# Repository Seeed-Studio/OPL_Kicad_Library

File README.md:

# Welcome to Our Hardware Component Repository!

Dive into a world of innovation with our curated collection of hardware components straight from the electronics hub of Shenzhen, complemented by an array of parts supported by Seeed Studio. Our mission is to empower makers, developers, and hardware enthusiasts with a diverse repository that streamlines innovation and accelerates development.

The Seeed Fusion Open Parts Libraries (OPL) and the associated component libraries are provided and maintained by the [Seeed Studio Fusion](https://www.seeedstudio.com/fusion.html) team and the wider community for the turnkey [Seeed Fusion PCB Assembly (PCBA) Service](https://www.seeedstudio.com/fusion_pcb.html).

**The XIAO Family**

To accelerate PCB design and make it much more convenient, Seeed Fusion has provided these component libraries for KiCad. Prepared and scrutinized by our own engineers, these footprints can save you hours of design time and minimize potential production errors, so you can get on with PCB design with peace of mind.

## Highlights(Content of Tables)

- [**Preparatory Work: KiCad Download and Library Download**](#jump1)
- [**How to add and use Seeed OPL Footprint Libraries(Grove Vision AI V2)**](#jump2)
- [**How to add and use Seeed OPL Symbol Libraries(Grove Vision AI V2)**](#jump3)
- [**Scale up Your Creation With Seeed Studio Fusion**](#jump4)
- [**Co-Create with Seeed Studio**](#jump5)
- [**Resources**](#jump6)

## <span id="jump1">Preparatory Work: KiCad Download and Library Download </span>

1. You can refer to this [link](https://www.kicad.org/download/) to download the KiCad software.

2. You can [download](https://github.com/Seeed-Studio/OPL_Kicad_Library) the "OPL_KiCad_Library" or use command to clone:

```
git clone https://github.com/Seeed-Studio/OPL_Kicad_Library.git
```

## How to add and use Seeed OPL Footprint Libraries

### <span id="jump2"> Take Grove Vision AI V2 and XIAO footprint as an Example </span>

1. Open KiCad and refer to `File -> Open Project`.

2. Find the "Grove Vision AI V2 Library" and open the project:

3. Double click the "Grove Vision AI V2" PCB file and you will see below:

4. Refer to the `Preferences -> Manage Footprint Libraries`

5. Here is the existed footprint libraries and you can click the button below:

6. Find the "Grove Vision AI V2 Library" and open the folder that contains the boards footprint:

Now you have added the "XIAO footprint library"

7. You can click here to use the added library:

8. Search for "seeed" and you can check the footprint added:

9. Click "ok" and you can add the XIAO RP2040 footprint into the "Grove Vision VI V2".

10. You can change any component on the Grove Vision VI V2 module and make it your own project.

## <span id="jump3"> How to add and use Seeed OPL Symbol Libraries </span>

### Take Grove Vision AI V2 and Sensor-Transducer as an Example:

1. Open KiCad and refer to `File -> Open Project`.

2. Find the "Grove Vision AI V2 Library" and open the project:

3. Double click the "Grove Vision AI V2" .sch file and you will see below:

4. Refer to the `Preferences -> Manage Symbol Libraries`

5. Here is the existed symbol libraries and you can click the button below:

6. Find the "OPL_Sensor-Transducer" lib file:

Now you have added the "OPL_Sensor-Transducer library"

7. You can click here to use the added library:

8. Search for "OPL" and you can check the symbol added:

9. Click "ok" and you can add it into the "Grove Vision VI V2".

10. You can change any component on the Grove Vision VI V2 module and make it your own project.

## <span id="jump4"> Scale up Your Creation With Seeed Studio Fusion </span>

Seeed Studio Fusion serves as the comprehensive service platform for Seeed Studio, a global one-stop online platform offering PCB manufacturing, PCB assembly and hardware customization with global sourcing capability. Whether you need prototyping, mass production, custom solutions for open-source products, or the transformation of your creative ideas into profitable products, Seeed Studio Fusion can meet your requirements.

- [PCB/PCBA Design](https://www.seeedstudio.com/fusion_pcb.html)
- [Fusion Website](https://www.seeedstudio.com/fusion.html)
- **Email Contact**: fusion@seeed.io

## <span id="jump5"> Co-Create with Seeed Studio </span>

Leverage our Co-Create Program to transform your advanced prototype into a commercially successful product! This program is designed to optimize your product's journey from prototype to market by handling marketing, packaging, and distribution, allowing you to concentrate on refining your product. Upon acceptance of your prototype by Seeed, it will be showcased on the Seeed Studio marketplace. You'll receive a portion of the profits for each unit sold.

- [Application Form](https://docs.google.com/forms/d/e/1FAIpQLSe3A7_rIbn2OLO4JyJd_poGZodItCaRy6M6-3FtdqL3xG1Usg/viewform)
- [Co-Create Website](https://www.seeedstudio.com/co-create.html)

## <span id="jump6"> Resources </span>

- [Seeed Studio Open Parts List](https://files.seeedstudio.com/wiki/OPL/OPL_list.xlsx)

<!-- ## Even More Components!

As of last December, the [OPL has expanded](http://www.seeedstudio.com/blog/2018/12/04/just-what-you-wanted-for-xmas-introducing-the-new-shenzhen-open-parts-library-with-over-10000-parts/) from 800 components to more than 10,000 with the introduction of the new Shenzhen OPL. The original Seeed OPL is a catalog of components from Seeed’s own inventory, we have the parts and, we have been using them in our own production processes for years. The Shenzhen OPL contains parts from Shenzhen’s biggest components distributor that Seeed can quickly order for turnkey PCBA. While the sources are different, both can be used together with the Seeed Fusion PCBA service and reduce the production time to 7 days.

But with all the new components and many more to come, we don’t have enough resources to create the footprints for all of them. So, we are asking for help from you and the wider community to gradually build-up the library with us. As more and more users utilize the OPL and update the component libraries, the better the library will become for everyone. 

To assist with the process, we have designated a team of engineers to maintain the library and GitHub repositories. They will also help draw some footprints and connect schematic symbols. But while our engineers do their best to check each footprint, with the sheer number of components, it is inevitable that some errors will be present. It is unavoidable. So to make up for it, Seeed Fusion has introduced a re-manufacture promise: If an error in the library requires the boards to be re-manufactured, then we will re-manufacture the corrected boards for you for free. By using this library, you accept this potential risk.

## Footprint Design Guidelines
It is still early days, and we have a lot of catching up to do. So, the most important additions at this stage are unique symbols and footprints and any generic footprints that are missing. Part-specific symbols that use generic footprints and slight variations of generic footprints can be added later.

For consistency and ease of use, we would greatly appreciate it if everyone followed the same guidelines for new additions to the library:

-	The previous component libraries have been re-organized to match the Shenzhen OPL’s categorization. Please add new entries to the relevant sub-library according to the online OPL library’s classification.
-	Please take the time to study [KiCad’s own Library Convention](http://kicad-pcb.org/libraries/klc/) and ensure that the new footprints comply. Please refer to other footprints in the OPL or KiCad’s built-in footprints for reference. 
-	For MPN specific footprints, please follow the existing footprint naming convention for the footprint and name the corresponding schematic symbol with the manufacturer part number.

### Notes:
- #### The current version of the KiCad Library has been completely revamped in response to all the feedback we have recieved. Originally a direct import of the Eagle library, the old library did not comply with KiCad guidelines and placed features on the wrong layers. For the latest version, we have throroughly investigated the issues and revised (nearly) all of the footprints. Let us know if you think we missed something!

-	The Seeed OPL component libraries have been updated to match the Shenzhen OPL categories to aid in merging the two libraries. Some components will have moved to new homes, but this has not been updated on the website OPL library yet. We will update this soon!
-	Some of the original Seeed OPL KiCad component footprints have not been updated to match KiCad’s design guidelines yet. They are safe to use, and the pads are correct, but they may look a little ugly.
-	Unlike previous versions, we have uploaded the files individually as opposed to a whole zip file. We hope this will help you follow standard GitHub workflow to contribute changes. (Thanks for your feedback!)

There is a lot to consider in managing a large library like this, so we would greatly appreciate any ideas and feedback regarding how we can make the library more user-friendly. We’ll be monitoring the discussion section and the designated OPL section in our forums. You are also welcome to let us know by [e-mail](mailto:fusion@seeed.cc).

We hope the new maintained library will prove to be an invaluable resource to all of our PCBA users and beyond.

## Resources
1. A KiCad Bill-of-Materials (BOM) plugin to follow SeeedStudio's Fusion PCBA assembly service's template, This plugin is set up to use the KiCad schematic's part data as it is provided in Seeed Studio's Open Parts Library (OPL) collection for KiCad. - https://github.com/imrehg/kicad-bom-seeedstudio

 -->

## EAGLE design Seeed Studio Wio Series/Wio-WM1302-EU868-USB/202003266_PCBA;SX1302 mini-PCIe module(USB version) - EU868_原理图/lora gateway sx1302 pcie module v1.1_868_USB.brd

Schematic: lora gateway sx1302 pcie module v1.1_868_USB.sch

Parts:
ANT1: U.FL-R-SMT-1(10); U-FL3P-SMD-2.6X2.6X1.0MM
ANT2: DNP; U-FL3P-SMD-2.6X2.6X1.0MM
C1, C12, C15, C19, C23, C25, C26, C29, C32, C41, C43, C45, C65, C67, C80, C83, C86, C88: 100nF; C0402
C2, C75: 2.2pF; C0402
C3, C92: 10uF; C0603
C4, C8, C11, C16, C17, C18, C64: 56pF; C0402
C5, C6, C9, C10: 3.6pF; C0402
C7, C91: 5.6pF; C0402
C13, C20, C21, C24, C28, C35, C39, C40, C42, C44, C47, C48, C76, C87, C89: 1uF; C0402
C14, C38, C57, C66, C81, C84: 10pF; C0402
C22, C27, C33: 10uF; C0603@1
C30, C56, C74, C77, C78, C79: DNP; C0402
C31: DNP; C0603@1
C34, C46, C63: 470nF; C0402
C36: 47nF; C0402
C37: 47pF; C0402
C49: 4.7uF; C0603
C50, C62, C85: 10nF; C0402
C51: 1nF; C0402
C52, C55: 100pF; C0402
C53, C60, C61: 3.3pF; C0402
C54: 39pF; C0402
C58: 1.3pF; C0402
C59, C68, C73: 1.8pF; C0402
C69, C70, C71, C72: 10uF; C0805
C82: 2.7pF; C0402
C90: 2.2uF; C0603
D1, D4: Green; LED-0402
D2: Red; LED-0402
D3: Blue; LED-0402
D5: LXES15AAA1-153; ESD-0402
D6: DNP; ESD-0402
D7: BAT54XV2T1G; SOD-523
FB1: BLM15PD121SN1D; F0402
J1: DNP; PCIE52P-0.8-50.95X30MM
L1: LQP15MN1N2B02D; L0402
L2: LQW15AN6N8G00D; L0402
L4: 0R; F0603
L5: LQH44PN1R0NP0L; L4.4X3.0MM
L6, L14, L20: MLZ2012M150WT; L0805
L7, L15, L18, L21: DNP; L0402
L8: LQW15AN3N0B00; L0402
L9: LQW15AN47NJ00D; L0402
L10: LQW15AN2N5B00D; L0402
L11: LQW15AN4N7C00D; L0402
L12, L13: LQW15AN12NG00D; L0402
L16: LQW15AN7N5G00D; L0402
L17, L24: LQW15AN5N6C10D; L0402
L22: LQW15AN15NG00D; L0402
Q8: CJ2101; SOT-323
Q10: CJ2102; SOT-323
R1, R4, R33, R34, R38, R42, R57, R65, R71: 10k; R0402
R2, R7: 0R; R0603
R3, R8, R11, R12, R43, R44, R46, R49, R51, R55, R56, R59, R60, R61, R62, R63, R67, R70, R72, R73, R74, R75, R76, R81: DNP; R0402
R5, R10, R14, R15, R16, R39, R40, R41: 100R; R0402
R6, R9, R37: 220R; R0402
R13, R35, R52: DNP; R0603
R17, R18, R19, R20, R21, R22, R23, R24, R25, R26, R27, R28, R29, R36, R45, R48, R50, R53, R54, R69, R77: 0R; R0402
R30, R31, R32: 680R; R0402
R47, R79: 1k; R0402
R58, R68: 4.7k; R0402
R64, R66: 22R; R0402
R78, R82: 100k; R0402
R80: 10R; R0402
R83, R87: 200k_1%; R0402
S1, S2, S3, S4, S5, S6: 323030226; SHIELD_CLIP
TP1, TP2, TP3, TP4, TP5, TP6, TP7, TP8, TP9, TP10, TP14: TEST-POINT-35; TP_3535
TP15: TEST-POINT'4545'; TP-D45MIL
U1: SX1302IMLTRT; QFN68-0.35-7X7X0.75MM
U2, U8, U10: HDF866A3-S6; FILTER6P-1.1-3X3X1.3MM
U3, U4: DNP; SOT-23-5
U5, U7: SX1250IMLTRT; QFN24G-0.5-4X4MM
U6: MP2161GJ; TSOT23-8
U9: SKY66420-11; MODULE16P-0.5-3X3X0.75MM
U11: SX1262IMLTRT; QFN24G-0.5-4X4MM
U12: STM32L412K8U6; UFQFPN32-0.5-5X5MM
U13: STTS751; UDFN-6L
X1: DSB221SDN; X4-SMD-2.5X2.0X1.0MM
X3: 32.768kHz; X2-SMD-3.2X1.5X0.55MM

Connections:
32MHZ: R6.2, R9.2, R37.2, X1.3 (OUT)
1302_CS: R33.2, R43.1, U1.1 (HOST_CSN), U12.10 (PA4)
1302_RESET: C1.2, D7.-, R1.2, U1.7 (RESET), U12.8 (PA2)
1302_RESET_HOST: D7.+, R59.1
CONFIG_OK: R31.1, U1.66 (GPIO0)
DM: J1.36, R66.1
DP: J1.38, R64.1
FEM_CS: R14.2, R34.1, U1.10 (RADIO_CTRL0), U3.3 (CE)
FEM_PA_ON: R15.2, U1.16 (RADIO_CTRL4)
GND: ANT1.GND1, ANT1.GND2, ANT2.GND1, ANT2.GND2, C2.1, C3.1, C5.1, C7.1, C9.1, C12.1, C13.1, C15.1, C16.1, C17.1, C18.1, C19.1, C20.1, C21.1, C22.1, C23.1, C24.1, C25.1, C26.1, C27.1, C28.1, C29.1, C30.1, C31.1, C32.1, C33.1, C34.1, C35.1, C36.1, C37.1, C39.1, C40.1, C41.1, C42.1, C43.1, C44.1, C45.1, C46.1, C47.1, C48.1, C49.1, C50.1, C51.1, C52.1, C55.1, C56.1, C57.1, C58.1, C60.2, C61.2, C62.1, C63.2, C65.2, C67.2, C69.1, C70.1, C71.1, C72.1, C73.2, C74.2, C76.1, C77.2, C78.2, C80.1, C81.2, C82.2, C83.1, C84.2, C85.1, C86.1, C87.1, C88.1, C89.1, C90.1, C92.1, D1.-, D2.-, D3.-, D4.-, D5.1, D6.1, J1.4 (GND), J1.9 (GND), J1.15 (GND), J1.18 (GND), J1.21 (GND), J1.26 (GND), J1.27 (GND), J1.29 (GND), J1.34 (GND), J1.35 (GND), J1.37 (GND), J1.40 (GND), J1.43 (GND), J1.50 (GND), J1.S1 (GND), J1.S2 (GND), Q10.2 (S), R1.1, R4.1, R11.1, R12.1, R17.2, R53.1, R53.2, R54.1, R54.2, R55.1, R55.2, R57.2, R73.1, R74.1, R74.2, R87.1, S1.S1, S1.S2, S1.S3, S1.S4, S1.S5, S2.S1, S2.S2, S2.S3, S2.S4, S2.S5, S3.S1, S3.S2, S3.S3, S3.S4, S3.S5, S4.S1, S4.S2, S4.S3, S4.S4, S4.S5, S5.S1, S5.S2, S5.S3, S5.S4, S5.S5, S6.S1, S6.S2, S6.S3, S6.S4, S6.S5, TP3.T, U1.6 (GND), U1.9 (GND), U1.15 (GND), U1.24 (GND), U1.25 (GND), U1.39 (GND), U1.46 (GND), U1.55 (GND), U1.62 (GND), U1.69 (GND), U2.1 (GND), U2.3 (GND), U2.4 (GND), U2.6 (GND), U3.2 (VSS), U4.2 (VSS), U5.7 (GND), U5.20 (GND), U5.PAD, U6.4 (PGND), U6.6 (AGND), U7.7 (GND), U7.20 (GND), U7.PAD, U8.1 (GND), U8.3 (GND), U8.4 (GND), U8.6 (GND), U9.10 (GND), U9.12 (GND), U9.17 (EPAD), U10.1 (GND), U10.3 (GND), U10.4 (GND), U10.6 (GND), U11.2 (GND), U11.5 (GND), U11.8 (GND), U11.20 (GND), U11.PAD, U12.16 (VSS), U12.32 (VSS), U12.PAD, U13.4 (ADDR/!THERM), U13.5 (GND), X1.2 (GND)
HOST_CS0: J1.51, R43.2
HOST_CS1: J1.25, R51.2
HOST_IO1: J1.33, R61.2
HOST_IO2: J1.31, R63.2
HOST_IO3: J1.23
HOST_IO4: J1.8, R67.2
HOST_IO5: J1.10, R60.2
HOST_IO6: J1.12
HOST_MISO: R39.1, R44.2
HOST_MOSI: J1.49, R46.2
HOST_RST: J1.22, R59.2, R77.2
HOST_SCK: J1.45, R49.2
I2C_SCL: R68.2, R76.1, R81.1, U12.29 (PB6), U13.1 (SCL)
I2C_SDA: R58.2, R70.1, R75.1, U12.30 (PB7), U13.6 (SDA)
MCU_RESET: C85.2, R71.2, R77.1, TP5.T, U12.4 (NRST)
MISO: R44.1, R45.1, U1.2 (HOST_MISO), U11.16 (MISO)
MISO_A: U1.42 (RADIO_A_MISO), U5.16 (MISO)
MISO_B: U1.33 (RADIO_B_MISO), U7.16 (MISO)
MOSI: R5.2, R40.2, R46.1, R48.1
MOSI_A: U1.67 (RADIO_A_MOSI), U5.17 (MOSI)
MOSI_B: U1.19 (RADIO_B_MOSI), U7.17 (MOSI)
unnamed: C11.2, U9.2 (RX)
unnamed: TP15.T, U6.1 (PG)
unnamed: C8.1, R11.2, R52.2, U8.5 (OUT)
unnamed: C2.2, L11.2, R52.1, U8.2 (IN)
unnamed: C11.1, R13.2, U2.2 (IN)
unnamed: C4.2, U9.1 (TX)
unnamed: C68.1, C74.1, C75.2
unnamed: C65.1, L18.2, R36.2, U11.1 (VDD_IN)
unnamed: C66.2, R37.1
unnamed: L5.1, U6.3 (SW)
unnamed: R83.1, R87.2, U6.7 (FB)
unnamed: R3.1, R4.2, X1.1 (ENABLE)
unnamed: C14.1, U5.3 (XTA)
unnamed: C62.2, L4.1, R3.2, X1.4 (VDD)
unnamed: R5.1, U1.3 (HOST_MOSI)
unnamed: D4.+, R47.2
unnamed: R10.1, U1.4 (HOST_SCK)
unnamed: R82.2, U6.8 (EN)
unnamed: R8.1, U4.3 (CE)
unnamed: C14.2, R6.1
unnamed: L6.2, U5.8 (DCC_SW)
unnamed: C34.2, L6.1, L7.2, U5.6 (VREG)
unnamed: C64.1, C82.1, L24.2
unnamed: R19.1, U1.34 (RADIO_B_CLK_I)
unnamed: C16.2, R14.1, U9.4 (CSD)
unnamed: C38.1, U7.3 (XTA)
unnamed: C36.2, C37.2, L9.2, U5.1 (VR_PA)
unnamed: C38.2, R9.1
unnamed: L14.2, U7.8 (DCC_SW)
unnamed: C46.2, L14.1, L15.2, U7.6 (VREG)
unnamed: C54.2, L11.1
unnamed: C7.2, C53.2, C54.1, L10.2
unnamed: C4.1, C8.2, R12.2
unnamed: C17.2, R15.1, U9.5 (CPS)
unnamed: C18.2, R16.1, U9.6 (CTX)
unnamed: R17.1, U1.20 (SP_VALID)
unnamed: R18.1, U1.32 (RADIO_B_IQ3)
unnamed: R20.1, U1.35 (RADIO_B_IQ0)
unnamed: R24.1, U1.41 (RADIO_A_IQ3)
unnamed: R21.1, U1.36 (RADIO_B_IQ1)
unnamed: R22.1, U1.37 (RADIO_B_IQ4)
unnamed: R23.1, U1.38 (RADIO_B_IQ2)
unnamed: R25.1, U1.43 (RADIO_A_CLK_I)
unnamed: R26.1, U1.44 (RADIO_A_IQ0)
unnamed: R27.1, U1.45 (RADIO_A_IQ1)
unnamed: R28.1, U1.48 (RADIO_A_IQ4)
unnamed: R29.1, U1.49 (RADIO_A_IQ2)
unnamed: D3.+, R32.2
unnamed: D2.+, R31.2
unnamed: D1.+, R30.2
unnamed: Q8.1 (G), Q10.3 (D), R78.2
unnamed: C1.1, R80.1
unnamed: L1.1, U9.16 (VCC1)
unnamed: L2.1, L8.1, U9.13 (PA_OUT)
unnamed: C56.2, C57.2, L8.2, L16.1
unnamed: C58.2, L16.2, U9.11 (TX_IN)
unnamed: C59.2, C60.1, L17.1, U9.9 (ANT)
unnamed: C61.1, C91.1, L17.2, L24.1
unnamed: C66.1, U11.3 (XTA)
unnamed: ANT1.D, C64.2, D5.2
unnamed: R35.2, R62.1, R69.2, U10.2 (IN)
unnamed: C63.1, L18.1, L20.1, U11.7 (VREG)
unnamed: R35.1, U9.7 (LNA_IN), U10.5 (OUT)
unnamed: L20.2, U11.9 (DCC_SW)
unnamed: J1.47, R39.2
unnamed: R40.1, U11.17 (MOSI)
unnamed: R41.1, U11.18 (SCK)
unnamed: C6.1, C10.1, C75.1, R13.1, U2.5 (OUT)
unnamed: R69.1, U9.8 (RX_FLT)
unnamed: C78.1, C79.1, L21.2
unnamed: ANT2.D, C79.2, D6.2
unnamed: C59.1, C91.2
unnamed: C77.1, L21.1, R62.2
unnamed: R65.2, U13.2 (!EVENT)
unnamed: C52.2, FB1.1, L1.2, U9.15 (VCC0)
unnamed: R64.2, U12.22 (PA12)
unnamed: R66.2, U12.21 (PA11)
unnamed: C92.2, Q10.1 (G), R79.2
unnamed: R56.2, R57.1, U12.31 (BOOT0)
unnamed: R72.2, R73.2, U12.6 (PA0-CLK_IN)
unnamed: C81.1, U12.2 (PC14-OSC32_IN), X3.2
unnamed: C84.1, U12.3 (PC15-OSC32_OUT), X3.1
unnamed: J1.14, R76.2
unnamed: J1.16, R70.2
unnamed: J1.30, R81.2
unnamed: J1.32, R75.2
PPS: J1.19, TP2.T, U1.8 (PPS), U12.27 (PB4)
RADIO_A_CLK_32M: R25.2, R72.1, U5.14 (BUSY)
RADIO_A_CLK_O: R28.2, U5.11 (DIO5)
RADIO_A_CSN: U1.68 (RADIO_A_CSN), U5.19 (NSS)
RADIO_A_IQ_0: R26.2, U5.13 (DIO1)
RADIO_A_IQ_1: R27.2, U5.12 (DIO2)
RADIO_A_IQ_2: R29.2, U5.5 (DIO3)
RADIO_A_IQ_3: R24.2, U5.21 (DIO4)
RADIO_A_RESET: U1.13 (RADIO_CTRL3), U5.15 (NRESET)
RADIO_A_RFIN: C6.2, L12.2, U5.23 (RFI_N)
RADIO_A_RFIP: C5.2, L12.1, U5.22 (RFI_P)
RADIO_B_CLK_32M: R19.2, U7.14 (BUSY)
RADIO_B_CLK_O: R22.2, U7.11 (DIO5)
RADIO_B_CSN: U1.18 (RADIO_B_CSN), U7.19 (NSS)
RADIO_B_IQ0: R20.2, U7.13 (DIO1)
RADIO_B_IQ_1: R21.2, U7.12 (DIO2)
RADIO_B_IQ_2: R23.2, U7.5 (DIO3)
RADIO_B_IQ_3: R18.2, U7.21 (DIO4)
RADIO_B_RESET: U1.28 (RADIO_CTRL9), U7.15 (NRESET)
RADIO_B_RFIN: C10.2, L13.2, U7.23 (RFI_N)
RADIO_B_RFIP: C9.2, L13.1, U7.22 (RFI_P)
RFO: C53.1, L9.1, L10.1, U5.24 (RFO)
RX_ON: R32.1, U1.59 (GPIO4)
SCK: R10.2, R41.2, R49.1, R50.1
SCK_A: U1.65 (RADIO_A_SCK), U5.18 (SCK)
SCK_B: U1.21 (RADIO_B_SCK), U7.18 (SCK)
STM32_MISO: R45.2, U12.12 (PA6)
STM32_MOSI: R48.2, U12.13 (PA7)
STM32_SCK: R50.2, U12.11 (PA5)
SWCLK: TP7.T, U12.24 (PA14)
SWDIO: TP8.T, U12.23 (PA13)
SX1261_BUSY: R67.1, U11.14 (BUSY), U12.9 (PA3)
SX1261_CS: R42.1, R51.1, U11.19 (NSS), U12.14 (PB0)
SX1261_IO1: R61.1, U1.54 (GPIO7), U11.13 (DIO1), U12.15 (PB1)
SX1261_IO2: R63.1, U11.12 (DIO2)
SX1261_IO3: TP9.T, U11.6 (DIO3)
SX1261_RFIN: C68.2, L22.2, U11.22 (RFI_N)
SX1261_RFIP: C73.1, L22.1, U11.21 (RFI_P)
SX1261_RST: R38.1, R60.1, U11.15 (NRESET), U12.18 (PA8)
SX1302_GPIO8: U1.53 (GPIO8), U12.26 (PB3)
TX_ON: R30.1, U1.63 (GPIO2)
TX_RX_SW: R16.2, U1.12 (RADIO_CTRL2)
VCCIO: C3.2, C19.2, C20.2, C25.2, C28.2, C41.2, C42.2, C45.2, C47.2, C76.2, C80.2, C83.2, C86.2, C87.2, C88.2, C89.2, C90.2, Q8.3 (D), R33.1, R34.2, R56.1, R58.1, R65.1, R68.1, R71.1, R80.2, TP1.T, U1.14 (VCC_IO), U1.30 (VCC_IO), U1.47 (VCC_IO), U1.61 (VCC_IO), U12.1 (VDD), U12.5 (VDDA), U12.17 (VDD), U13.3 (VDD)
VCC_1V2: C12.2, C13.2, C23.2, C24.2, C29.2, C40.2, C43.2, C44.2, C71.2, C72.2, L5.2, R79.1, R83.2, TP14.T, U1.5 (VCC_CORE), U1.23 (VCC_CORE), U1.40 (VCC_CORE), U1.56 (VCC_CORE), U6.5 (OUT)
VCC_FEM: C26.2, C27.2, C49.2, C50.2, C51.2, C55.2, FB1.2, L2.2, R2.2, TP6.T, U3.5 (VOUT)
VCC_RADIO: C21.2, C32.2, C33.2, C35.2, C39.2, C48.2, C67.1, L4.2, L7.1, L15.1, R7.2, R36.1, R38.2, R42.2, TP10.T, U4.5 (VOUT), U5.2 (VDD_IN), U5.9 (VBAT_RF), U5.10 (VBAT_DIO), U7.2 (VDD_IN), U7.9 (VBAT_RF), U7.10 (VBAT_DIO), U11.10 (VBAT), U11.11 (VBAT_IO)
VIN: C15.2, C22.2, C30.2, C31.2, C69.2, C70.2, J1.2 (3V3), J1.24 (3V3), J1.39 (3V3), J1.41 (3V3), J1.52 (3V3), Q8.2 (S), R2.1, R7.1, R8.2, R47.1, R78.1, R82.1, TP4.T, U3.1 (VIN), U4.1 (VIN), U6.2 (VIN)

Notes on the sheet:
V1.0
Initial Release
2020/01/02
Vincent
50ohm Impedence
3.3V
300mA
1.2V
500mA
100mA
USB
868
915
SPI
For Power-up delay
V1.1
Add power up delay circuit at VCCIO
Add power up reset circuit for SX1302
Change pins refer to Semtech V3 Schematic
2021/02/18

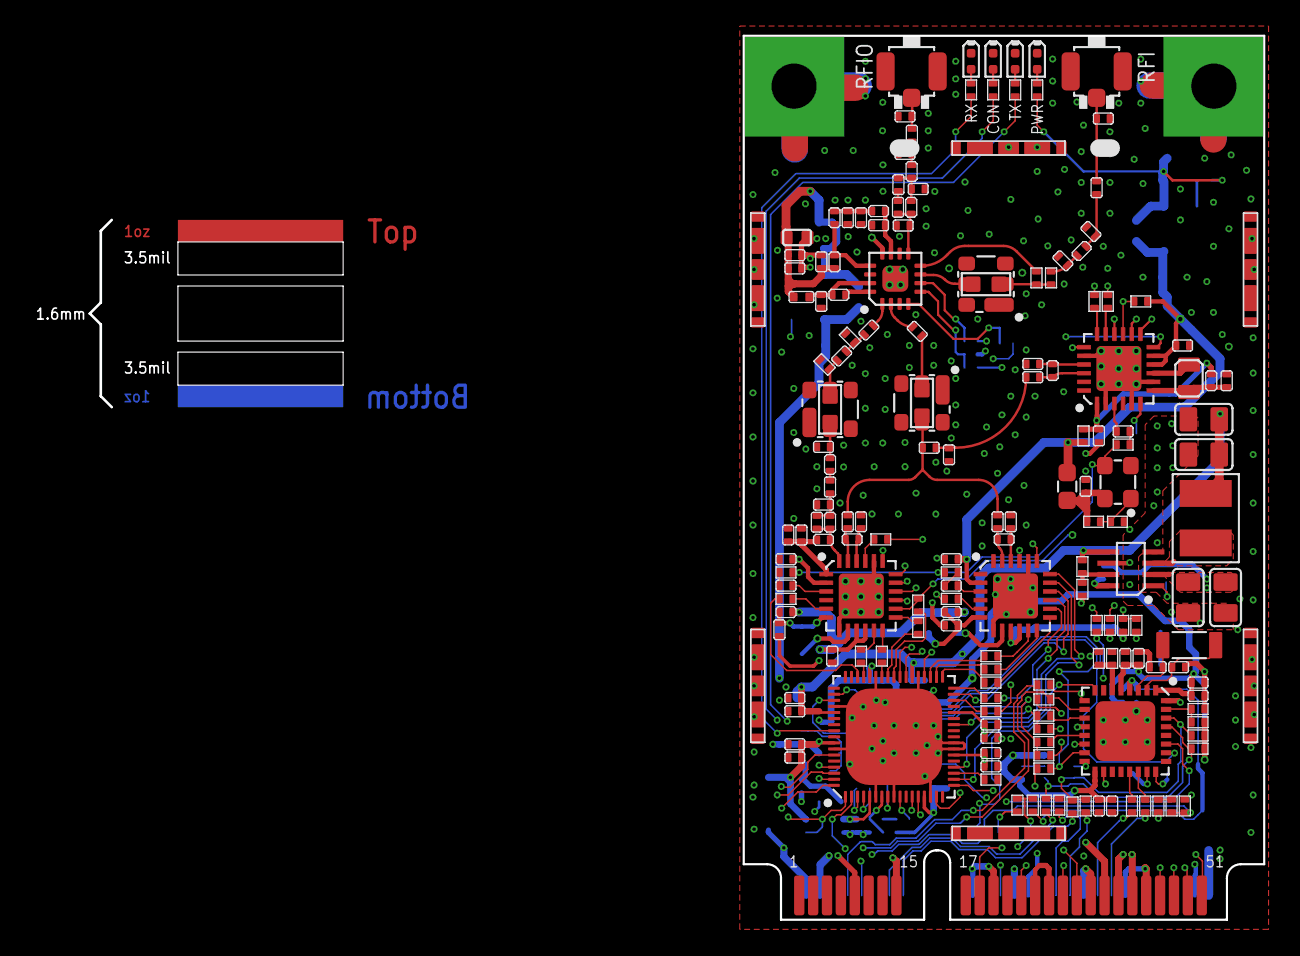
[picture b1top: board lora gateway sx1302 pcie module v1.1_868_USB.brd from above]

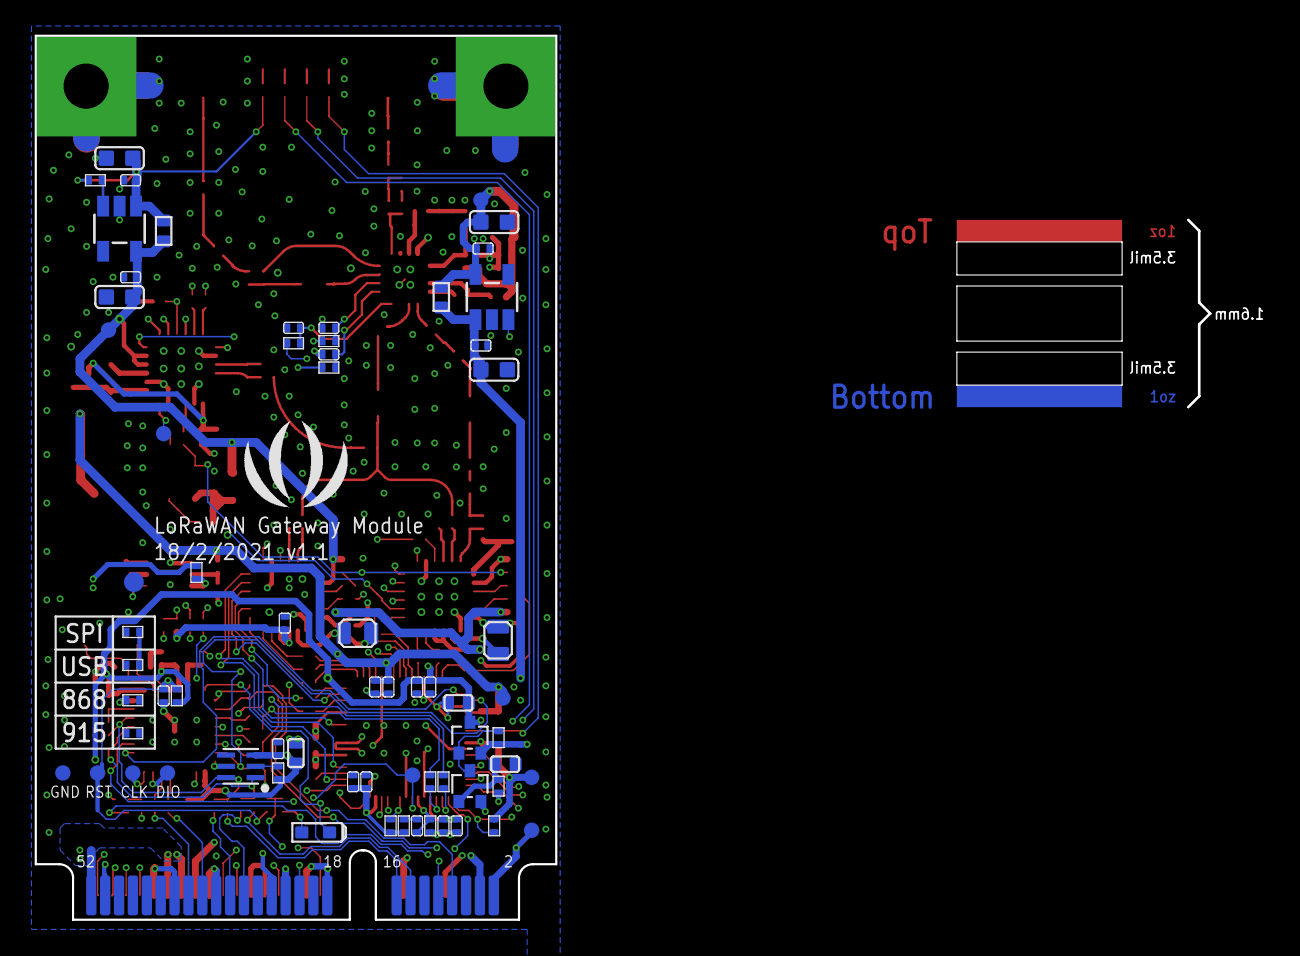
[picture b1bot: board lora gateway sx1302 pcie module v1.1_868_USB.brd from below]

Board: 4 copper layers, 30.0 x 51.0 mm, 244 parts (68 on the bottom side), 162 nets.

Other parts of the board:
U$45: SEEED-SILK-TNAME-280*268MIL

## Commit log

2017-12-01 Correct micro-USB connector footprint
    1. Corrected Micro-USB footprint drill hole from circular shape to oval xdim:0.5mm, ydim:1.2mm.
    2. This was following sample footprint recommendations from the FCI 10118193-0001LF datasheet.
    3. Without the modification there is a collision with the FCI model step file and the PCB drill hole.
    4. Additional checks will have to be done to assess if this is compatible with the Suntech connectors.
2018-11-27 Update the footprint of connectors and capacitors
2019-01-10 Create Seeed_Fusion_PCBA_OPL_Component_Library_for_KiCad\
2019-01-10 Create txt
2019-01-11 Updated OPL_Circuit_Protection
2019-02-14 Added OPL Excel spreadsheet
    This spreadsheet contains all the parts in the Seeed and Shenzhen OPL as of 2019-02-14. It also contains keyword translations for many parts in the Shenzhen OPL that are not currently updated in the 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
2019-05-03 added ceramic 2.2uF 0805 & 0603
2019-06-11 added SMD-CRYSTAL-8MHZ-18PF-10PPM-80R_HC49US_
2019-06-11 added CERAMIC-33PF-50V-5%-NPO_0402_
2019-06-11 CERAMIC-18PF-50V-5%-NPO_0402_
2019-06-11 added CERAMIC-12PF-50V-5%-NPO_0402_
2019-06-12 footprint filter for SMD-CRYSTAL-8MHZ-18PF-10PPM-80R_HC49S_
2019-06-12 added CERAMIC-20PF-50V-5%-NPO_0402_
2019-06-18 TANTALUM-SMD-10UF-10V-10%_AVX-A_ pins renamed (fixes #17)
    + -> 1
    - -> 2
2019-06-18 added CERAMIC-1UF-25V-10%-X7R_0603_
2019-08-10 ZX62B micro usb connector: Don't hide pin names in schematic
2020-05-14 Add URLs to datasheets
    Used the following python script to add URLs to all library components:
    import re
    import argparse
    import io
    argparser = argparse.ArgumentParser()
    argparser.add_argument("files", nargs='+')
2024-01-22 Add: Grove Vision AI V2 Kicad
2024-01-24 Update: update contents
2024-01-24 Add: Add Grove Vision AI V2 BOM file
2024-01-26 Add: add required files
2024-03-08 Add: add wio series files
2024-03-23 Add: Add XIAO nRF52840 symbol to `Seeed_Studio_XIAO_Series.kicad_sym`.
    Could not confirm from pinout diagram which NFC pad is NFC1/NFC2 but should not impact usage for NFC antenna.
2024-05-29 Update: update Grove modules KiCAD libraries
2024-10-08 Add sync_issues GitHub Action for workflows
2024-10-14 Update: update XIAO series footprint
2024-10-15 Add: Add wio-sx1262 module
2024-11-25 Fix: XIAO Name
2024-12-29 Minor spelling corrections for README.md
2025-01-08 ci: add an action to automatically close stale issues and PRs
2025-09-05 Update wio LR1121 files
2025-09-08 Add KiCAD files
2025-09-23 Add the XIAO Family KiCAD
2025-09-23 Add XIAO Family KiCAD
2025-09-24 Update: update XIAO family and related files
2025-09-25 Update XIAO Series family images and files
2025-11-24 Add Creative Commons License
    Added the Creative Commons Attribution-ShareAlike 4.0 International Public License to the project.
2025-12-29 Fix XIAO ESP32C6 symbol Value property
2026-03-18 Add new KiCad footprints for XIAO series variants
2026-04-17 Update the footprint and symbol files for the XIAO ESP32-S3 Plus
2026-04-17 Update the footprint and symbol files for the XIAO ESP32-S3 Plus (#37)
2026-05-17 Remap battery pins in esp32c6 library
    The symbol and footprints had different pin numbers, this changes the symbol to match BAT+ for pin 24 and BAT- for pin 23 (instead of 33 and 34, which did not have corresponding pads)
2026-05-18 Fix pins in Seeed_Studio_XIAO_Series.kicad_sym
2026-06-23 add:xiao series library
2026-06-23 fix:The original file is incorrect
2026-06-23 add:xiao series library (#39)
    * add:xiao series library
    * fix:The original file is incorrect
